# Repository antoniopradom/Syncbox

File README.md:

# Syncbox

This is syncbox that was designed to worked with as many devices as possible. It can sync TTL signals, wifi devices, motion capture cameras (e.g. Vicon), video cameras (using red LED). It can be daisy-chained with multiple devices or other syncboxes.

It has 2 operations modes:

1. Main: Receives a high TTL signal, then broadcasts a UDP packet (repeated 5 times for prevent packet loss) that can be captured by any WIFI enabled device. As long as the signal is high, the LEDs will be on. This allows to sync cameras. When the TTL signal goes low, a stop sync UDP packet is sent and the LEDs are turned off.
1. Receiver: When a box set to main mode broadcasts the sync UDP packet, the receiver turns on the LEDs and generates a TTL signal that allows syncing devices that are not WIFI enabled. When the sync end UDP packet is received, the TTL goes low and the LEDs turn off.

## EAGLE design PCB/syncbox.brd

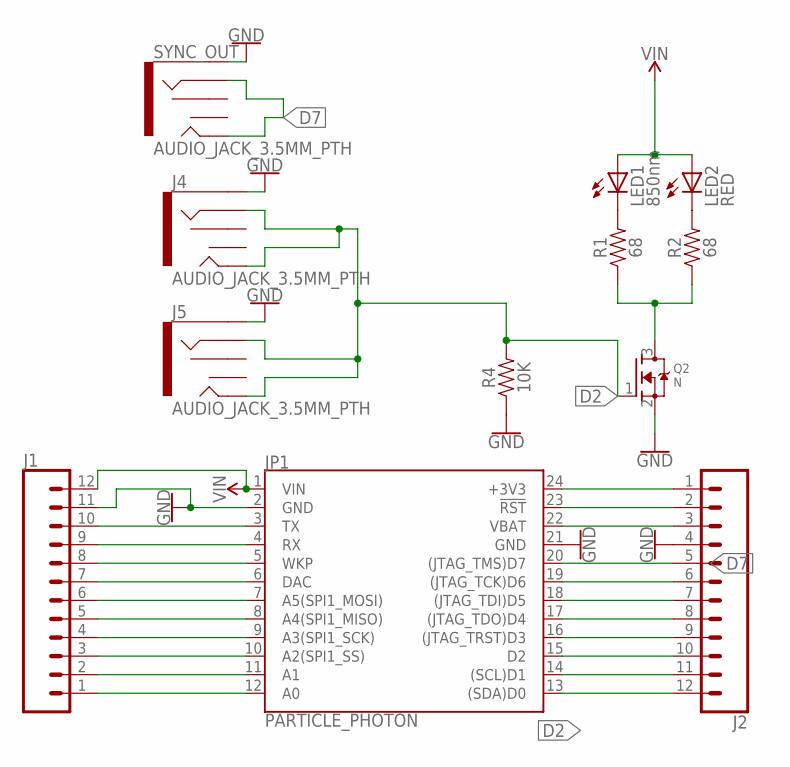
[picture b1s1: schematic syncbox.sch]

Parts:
J1, J2: CONN_12; 1X12
J4, J5: AUDIO_JACK_3.5MM_PTH; AUDIO-JACK
JP1: PARTICLE_PHOTON
LED1: 850nm; LED5MM
LED2: RED; LED5MM
Q2: N; SOT23-W
R1, R2: 68; AXIAL-0.3
R4: 10K; AXIAL-0.3
SYNC_OUT: AUDIO_JACK_3.5MM_PTH; AUDIO-JACK

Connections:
D2: J2.10, J4.RING, J4.TIP, J5.RING, J5.TIP, JP1.15 (D2), Q2.1 (G), R4.P$2 (2)
D7: J2.5, JP1.20 ((JTAG_TMS)D7), SYNC_OUT.RING, SYNC_OUT.TIP
GND: J1.11, J2.4, J4.SLEEVE, J5.SLEEVE, JP1.2 (GND), JP1.21 (GND), Q2.2 (S), R4.P$1 (1), SYNC_OUT.SLEEVE
unnamed: LED1.K (C), R1.P$2 (2)
unnamed: LED2.K (C), R2.P$2 (2)
unnamed: Q2.3 (D), R1.P$1 (1), R2.P$1 (1)
unnamed: J1.10, JP1.3 (TX)
unnamed: J1.9, JP1.4 (RX)
unnamed: J2.12, JP1.13 ((SDA)D0)
unnamed: J1.8, JP1.5 (WKP)
unnamed: J1.7, JP1.6 (DAC)
unnamed: J1.6, JP1.7 (A5(SPI1_MOSI))
unnamed: J1.5, JP1.8 (A4(SPI1_MISO))
unnamed: J1.4, JP1.9 (A3(SPI1_SCK))
unnamed: J1.3, JP1.10 (A2(SPI1_SS))
unnamed: J1.2, JP1.11 (A1)
unnamed: J1.1, JP1.12 (A0)
unnamed: J2.11, JP1.14 ((SCL)D1)
unnamed: J2.9, JP1.16 ((JTAG_TRST)D3)
unnamed: J2.8, JP1.17 ((JTAG_TDO)D4)
unnamed: J2.7, JP1.18 ((JTAG_TDI)D5)
unnamed: J2.6, JP1.19 ((JTAG_TCK)D6)
unnamed: J2.3, JP1.22 (VBAT)
unnamed: J2.2, JP1.23 (!RST!)
unnamed: J2.1, JP1.24 (+3V3)
VIN: J1.12, JP1.1 (VIN), LED1.A, LED2.A

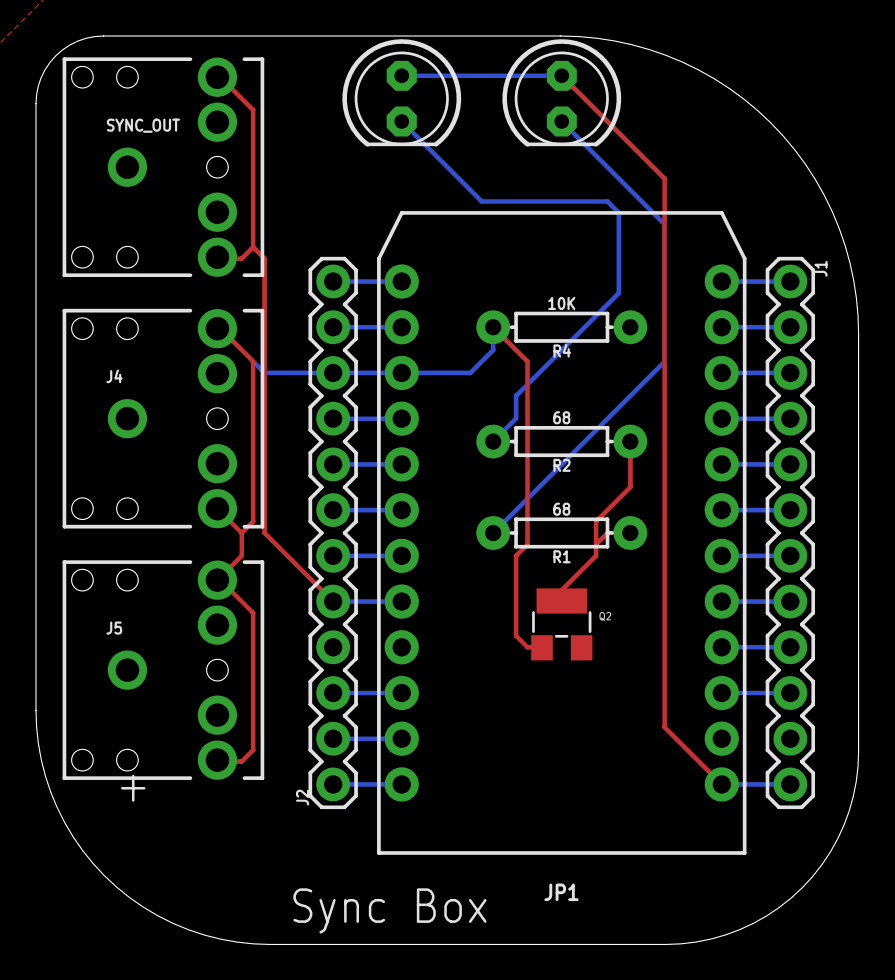
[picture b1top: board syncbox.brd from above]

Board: 2 copper layers, 45.7 x 50.5 mm, 12 parts (0 on the bottom side), 26 nets.

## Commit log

2024-07-09 Added files

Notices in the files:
parts and their libraries:
SparkFun-Boards: Licensing: Creative Commons ShareAlike 4.0 International - https://creativecommons.org/licenses/by-sa/4.0
